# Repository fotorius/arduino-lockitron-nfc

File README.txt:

Author:   Alfredo Rius
License:  BSD(LICENSE)

    This is an implementation of the NFC breakout for the PN532 from Adafruit
    and the Lockitron platform to allow access to doors.

    This program is based on the readMifare.pde from Adafruit. It takes the
    first 4 bytes of a Mifare card uid and compares it to flash memory. Since
    it is saved to the flash, it will remember all cards even if the arduino
    is disconnected.

    This program is based on the arduino-lockitron-nfc shield located (Eagle
    files in https://github.com/devalfrz/arduino-lockitron-nfc).

    Buttons: (buttons are set to have a pullup resistor so they ar inverted)
      - LOCK_UNLOCK: This button will lock or unlock the system depending on its
          previous state.
          
      - SAVE_CARD: If it's pressed for 3 seconds while a card is read,
          it will either save the current card and blink 3 times or delete the
          card and blink one time for 2 seconds.
          
      - RESET_MEMORY: Keep this button pressed and this will clear all cards in
          memory.

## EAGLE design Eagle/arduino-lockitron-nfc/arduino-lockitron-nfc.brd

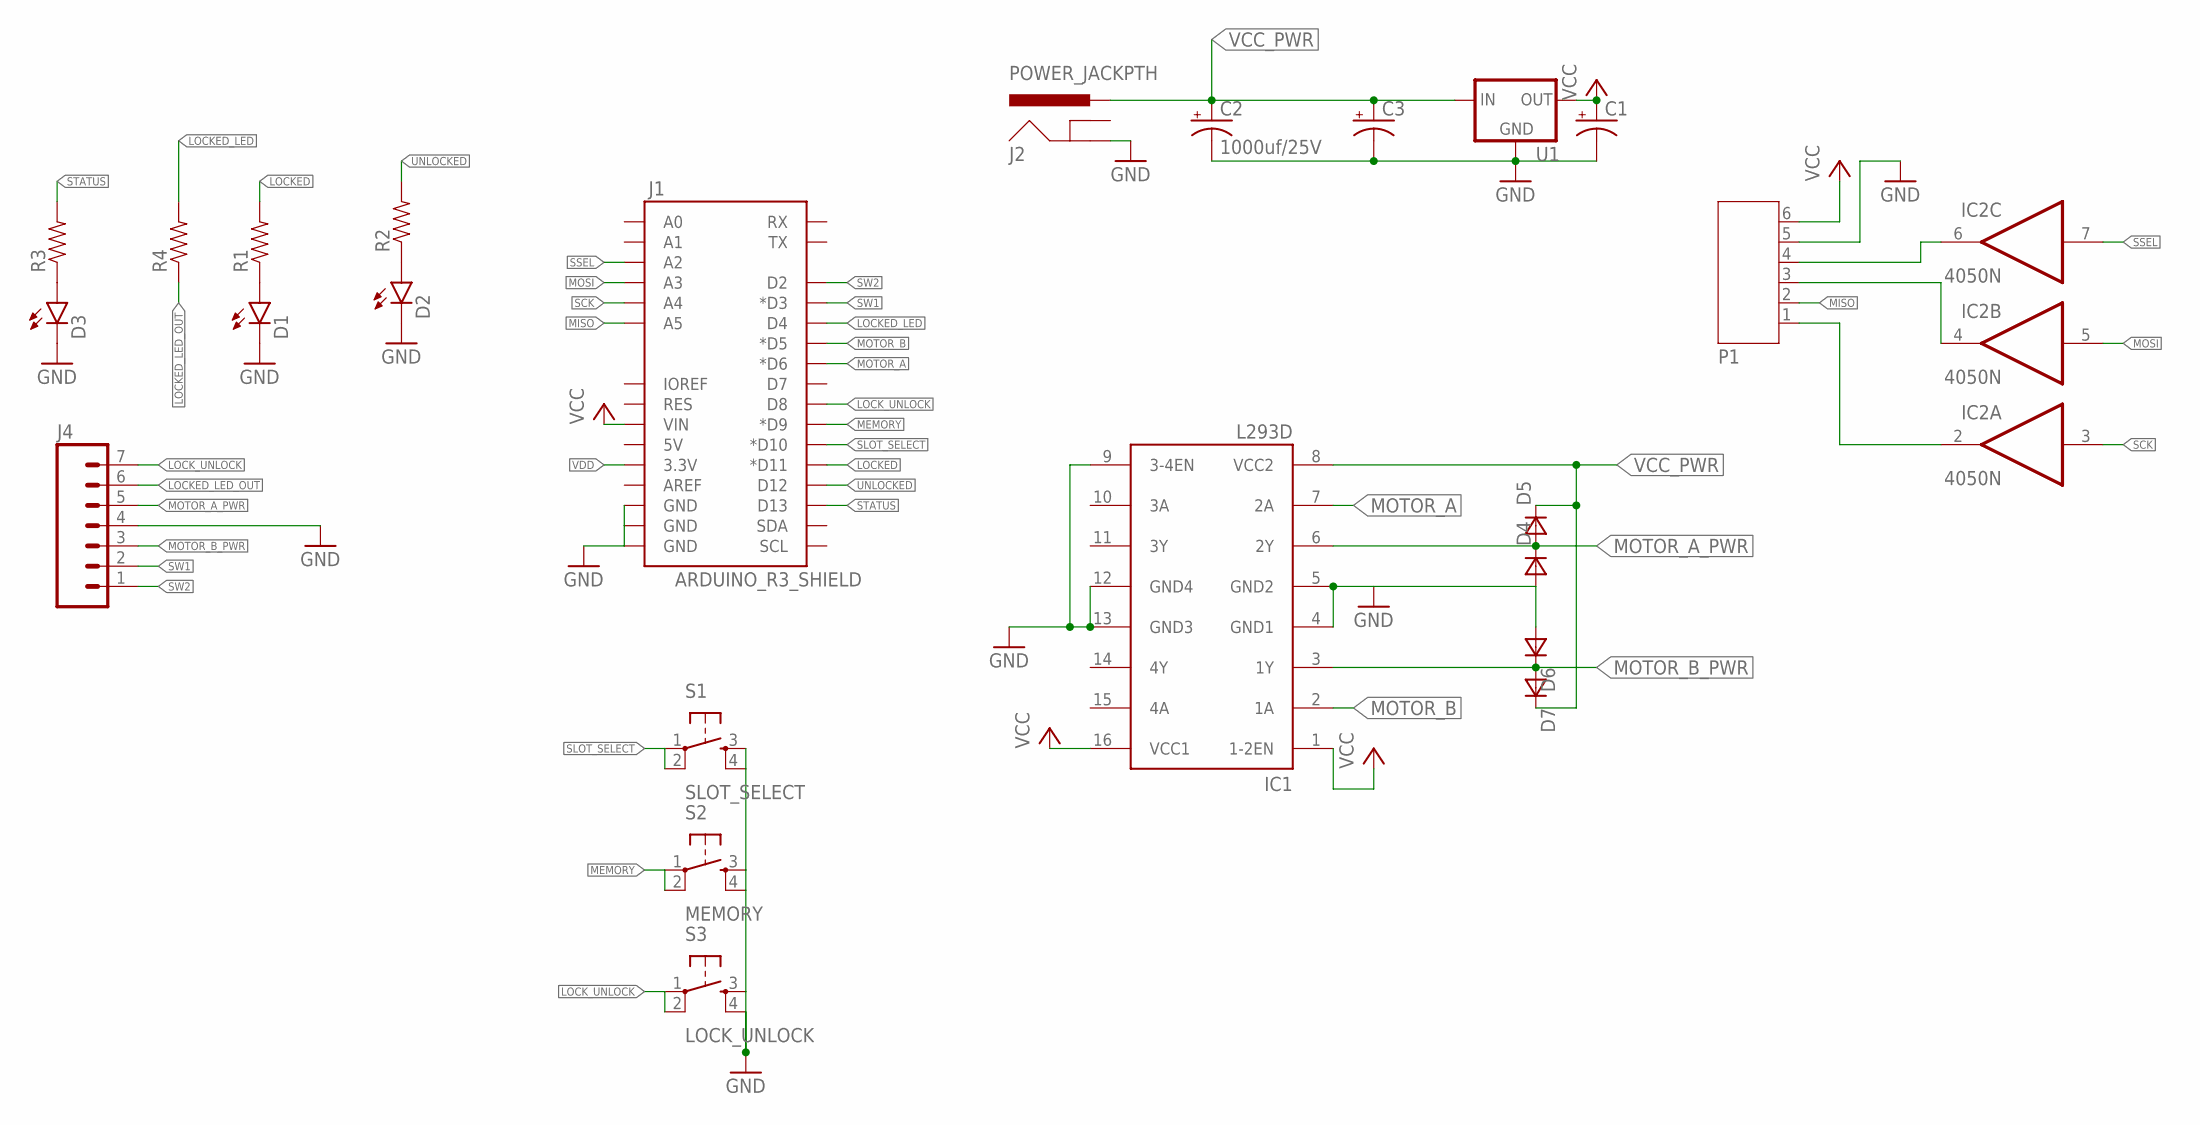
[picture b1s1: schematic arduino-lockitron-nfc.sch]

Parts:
C1, C3: 47UF-50V-20%(ELECT); PANASONIC_D
C2: 1000uf/25V; CPOL-RADIAL-1000UF-25V-KIT
D1, D2, D3: LED0603; LED-0603
D4, D5, D6, D7: DSOD323; SOD323
IC1: L293D; DIL16
IC2: 4050N; DIL16
J1: ARDUINO_R3_SHIELD; UNO_R3_SHIELD
J2: POWER_JACKPTH; POWER_JACK_PTH
J4: M07LONGPADS; 1X07_LONGPADS
P1: JST-PH6
R1, R2, R3, R4: RESISTOR0603; 0603-RES
S1: SLOT_SELECT; TACTILE-SWITCH-SMD
S2: MEMORY; TACTILE-SWITCH-SMD
S3: LOCK_UNLOCK; TACTILE-SWITCH-SMD
U1: V_REG_78XXSIDE; 78XXL

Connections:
LOCKED: J1.D11 (*D11), R1.2
LOCKED_LED: J1.D4, R4.2
LOCKED_LED_OUT: J4.6, R4.1
LOCK_UNLOCK: J1.D8, J4.7, S3.1, S3.2
MEMORY: J1.D9 (*D9), S2.1, S2.2
MISO: J1.A5, P1.2
MOSI: IC2.5 (I), J1.A3
MOTOR_A: IC1.7 (2A), J1.D6 (*D6)
MOTOR_A_PWR: D4.1 (C), D5.2 (A), IC1.6 (2Y), J4.5
MOTOR_B: IC1.2 (1A), J1.D5 (*D5)
MOTOR_B_PWR: D6.1 (C), D7.2 (A), IC1.3 (1Y), J4.3
unnamed: IC2.2 (O), P1.1
unnamed: IC2.4 (O), P1.3
unnamed: IC2.6 (O), P1.4
unnamed: D1.A, R1.1
unnamed: D3.A, R3.1
unnamed: D2.A, R2.1
SCK: IC2.3 (I), J1.A4
SLOT_SELECT: J1.D10 (*D10), S1.1, S1.2
SSEL: IC2.7 (I), J1.A2
STATUS: J1.D13, R3.2
SW1: J1.D3 (*D3), J4.2
SW2: J1.D2, J4.1
UNLOCKED: J1.D12, R2.2
VCC: C1.+, IC1.1 (1-2EN), IC1.16 (VCC1), J1.VIN, P1.6, U1.OUT
VCC_PWR: C2.+, C3.+, D5.1 (C), D7.1 (C), IC1.8 (VCC2), J2.PWR, U1.IN
VDD: IC2.1 (VDD), J1.3.3V
VSS: C1.-, C2.-, C3.-, D1.C, D2.C, D3.C, D4.2 (A), D6.2 (A), IC1.4 (GND1), IC1.5 (GND2), IC1.9 (3-4EN), IC1.12 (GND4), IC1.13 (GND3), IC2.8 (VSS), J1.GND@0 (GND), J1.GND@1 (GND), J1.GND@2 (GND), J2.GND, J4.4, P1.5, S1.3, S1.4, S2.3, S2.4, S3.3, S3.4, U1.GND

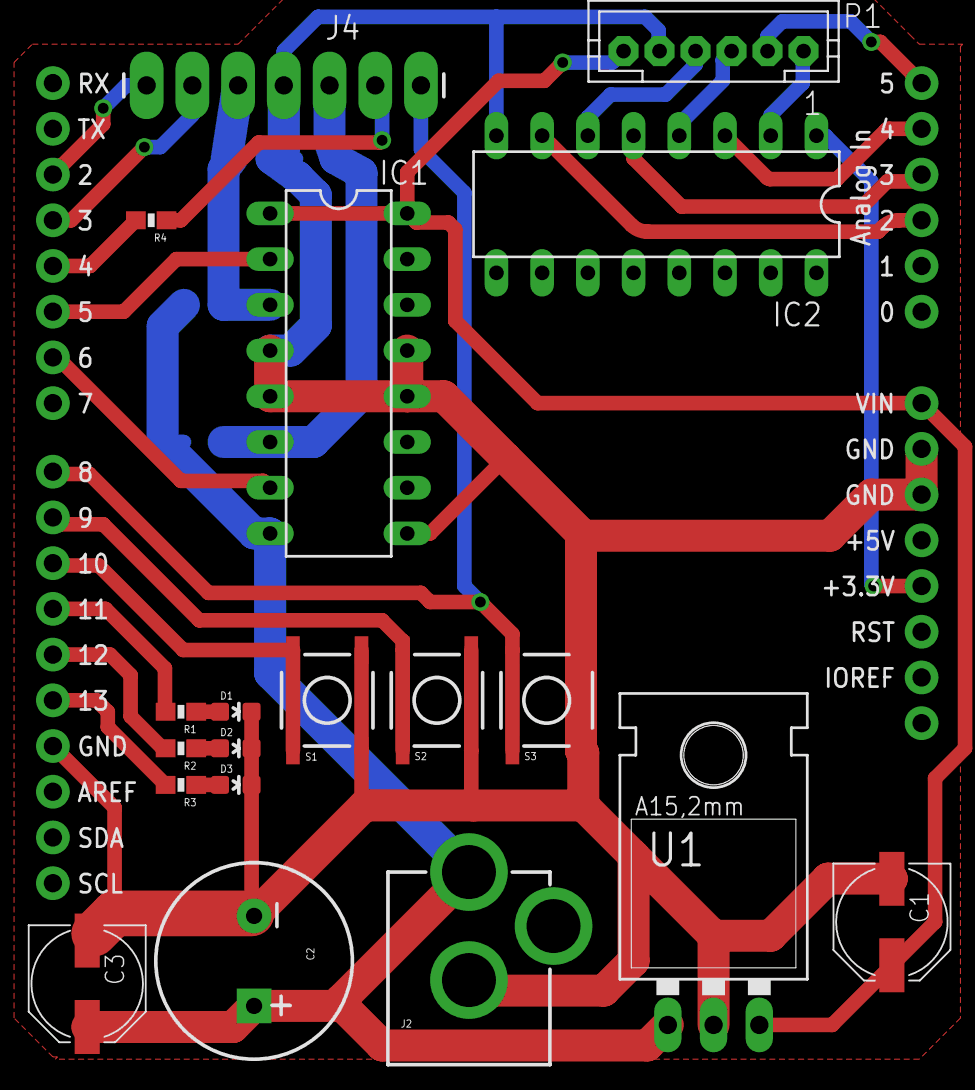
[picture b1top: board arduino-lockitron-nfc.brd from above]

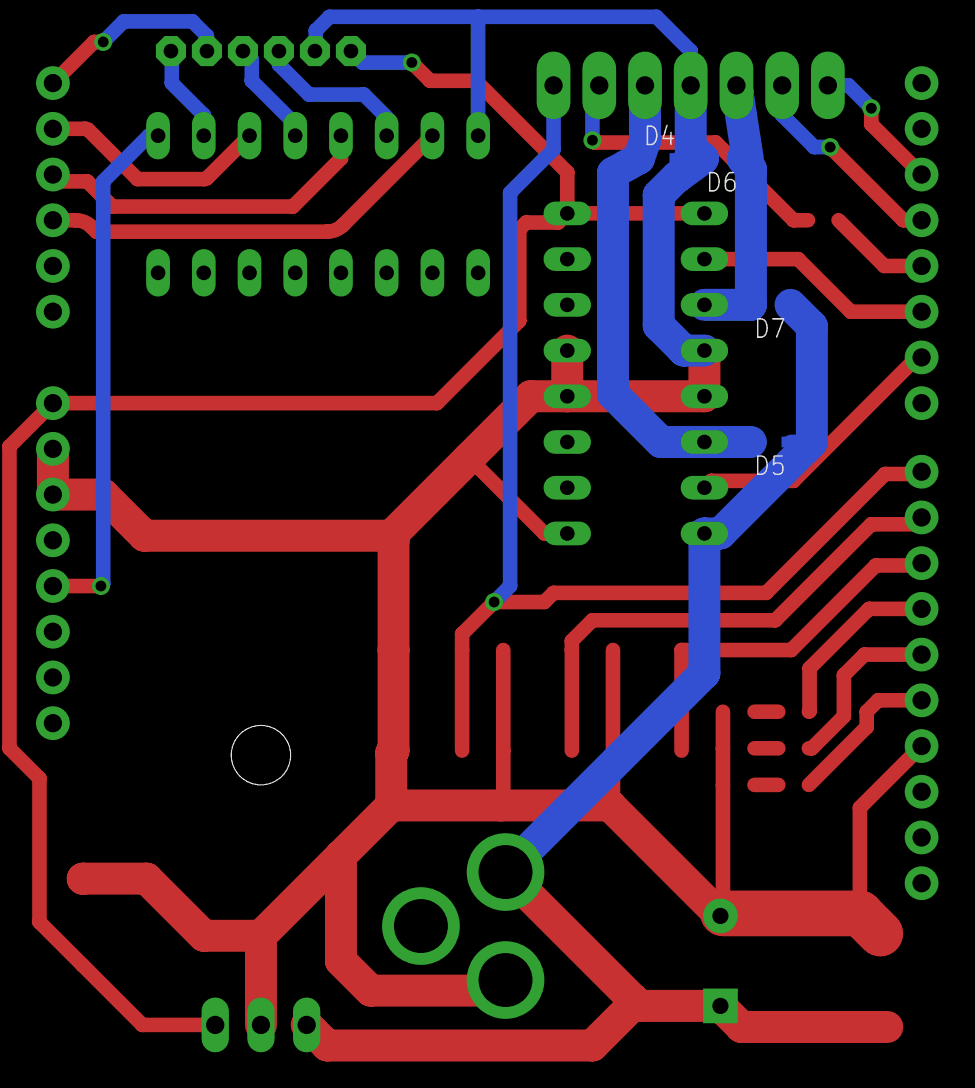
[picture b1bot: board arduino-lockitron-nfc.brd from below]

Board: 2 copper layers, 24 parts (4 on the bottom side), 28 nets.

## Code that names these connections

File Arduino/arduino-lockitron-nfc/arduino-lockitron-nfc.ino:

/**************************************************************************/
/*! 
    @file     arduino-lockitron-nfc
    @author   Alfredo Rius
    @license  BSD

    This is an implementation of the NFC breakout for the PN532 from Adafruit
    and the Lockitron platform to allow access to doors.

    This program is based on the arduino-lockitron-nfc shield located (Eagle
    files in https://github.com/devalfrz/arduino-lockitron-nfc).

    Buttons: (buttons are set to have a pullup resistor so they ar inverted)
      - LOCK_UNLOCK: This button will lock or unlock the system depending on its
          previous state.
          
      - SAVE_CARD: If it's pressed for 3 seconds while a card is read,
          it will either save the current card and blink 3 times or delete the
          card and blink one time for 2 seconds.
          
      - RESET_MEMORY: Keep this button pressed and this will clear all cards in
          memory.
          

*/
/**************************************************************************/

/**** INPUTS/OUTPUTS ****/
// Adafruit PN532 breakout board:
#define PN532_SCK  A4
#define PN532_MOSI A3
#define PN532_SS   A2
#define PN532_MISO A5
// Buttons
#define SLOT_SELECT 10
#define SAVE_CARD 9
#define STATUS_LED 13
#define UNLOCKED 12
#define LOCKED 11
// Lockitron
#define MOTOR_A 6
#define MOTOR_B 5
#define SW1 2
#define SW2 3
#define LOCK_UNLOCK 8

/**** Other definitions ****/
#define TOTAL_SLOTS 64 // Arbitrary number of slots available
#define SLOT_SIZE 4
//#define DEBUG // Will show output on terminal



#include <Wire.h>
#include <SPI.h>
#include <Adafruit_PN532.h>
#include <EEPROM.h>


// Adafruit PN532 init SPI
Adafruit_PN532 nfc(PN532_SCK, PN532_MISO, PN532_MOSI, PN532_SS);


int memory_slot = 0;
boolean state = 0;


void setup(void) {
  pinMode(SAVE_CARD,INPUT_PULLUP);
  pinMode(SLOT_SELECT,INPUT_PULLUP);
  pinMode(STATUS_LED,OUTPUT);
  pinMode(LOCKED,OUTPUT);
  pinMode(UNLOCKED,OUTPUT);
  pinMode(SW1,INPUT_PULLUP);
  pinMode(SW2,INPUT_PULLUP);
  pinMode(LOCK_UNLOCK,INPUT_PULLUP);
  pinMode(MOTOR_A,OUTPUT);
  pinMode(MOTOR_B,OUTPUT);
  
  #ifdef DEBUG
  Serial.begin(115200);
  #endif

  nfc.begin();

  uint32_t versiondata = nfc.getFirmwareVersion();
  if (! versiondata) {
    #ifdef DEBUG
    Serial.print("Didn't find PN53x board");
    #endif
    digitalWrite(STATUS_LED,HIGH);
    while (1); // halt
  }
  #ifdef DEBUG
  // Got ok data, print it out!
  Serial.print("Found chip PN5"); Serial.println((versiondata>>24) & 0xFF, HEX); 
  Serial.print("Firmware ver. "); Serial.print((versiondata>>16) & 0xFF, DEC); 
  Serial.print('.'); Serial.println((versiondata>>8) & 0xFF, DEC);
  #endif
  
  // configure board to read RFID tags
  nfc.SAMConfig();
}


void loop(void) {
  uint8_t success;
  uint8_t uid[] = { 0, 0, 0, 0, 0, 0, 0 };  // Buffer to store the returned UID
  uint8_t uidLength;    // Length of the UID (4 or 7 bytes depending on ISO14443A card type)
  int i,j;
  boolean save_delete = 0;
  boolean access_granted = 0;
  
  // Wait for an ISO14443A type cards (Mifare, etc.).  When one is found
  // 'uid' will be populated with the UID, and uidLength will indicate
  // if the uid is 4 bytes (Mifare Classic) or 7 bytes (Mifare Ultralight)
  success = nfc.readPassiveTargetID(PN532_MIFARE_ISO14443A, uid, &uidLength,100);
  
  save_delete = (success && !digitalRead(SAVE_CARD)) ? 1 : 0;
  
  if (success) {
    digitalWrite(STATUS_LED,HIGH);
    delay(100);
    digitalWrite(STATUS_LED,LOW);
    #ifdef DEBUG
    // Display some basic information about the card
    Serial.println("Found an ISO14443A card");
    Serial.print("  UID Length: ");Serial.print(uidLength, DEC);Serial.println(" bytes");
    Serial.print("  UID Value: ");
    nfc.PrintHex(uid, uidLength);
    Serial.println("");
    #endif
    memory_slot = check_card(uid);
    access_granted = (memory_slot == -1) ? 0 : 1;
    
    if(save_delete){
      access_granted = 0; //Reset Access
      #ifdef DEBUG
      Serial.println("Continue pressing to save or delete card");
      #endif
      delay(3000);
      if(!digitalRead(SAVE_CARD)){
        if(memory_slot == -1){
          memory_slot = save_card(uid);
          #ifdef DEBUG
          Serial.print("Save Card Slot: ");
          Serial.println(memory_slot+1);
          blink_n_times(memory_slot+1,STATUS_LED,250);
          delay(1000);
          #endif
          blink_n_times(3,STATUS_LED,100);
        }else{
          delete_card(memory_slot);
          #ifdef DEBUG
          Serial.println("Card deleted!");
          #endif
          blink_n_times(1,STATUS_LED,2000);
        }
      }
    }
    if(access_granted){
      #ifdef DEBUG
      Serial.println("Access Granted");
      #endif

      // Lock/Unlock system.
      digitalWrite(STATUS_LED,HIGH);
      state = lock(!state);
      digitalWrite(STATUS_LED,LOW);
      delay(100);
      #ifdef DEBUG
        if(check_card(uid)) blink_n_times(i+1,STATUS_LED,250); 
      #endif
    }else{
      #ifdef DEBUG
      Serial.println("Access Denied");
      #endif
    }
    access_granted = 0; //Reset Access
  }
  if(!digitalRead(LOCK_UNLOCK)){// Unlock or lock door
    state = lock(!state);
  }
  if(!digitalRead(RESET_MEMORY)){// Swipe memory
    digitalWrite(STATUS_LED,HIGH);
    delay(5000);
    digitalWrite(STATUS_LED,LOW);
    if(!digitalRead(RESET_MEMORY)){
      clear_memory();
      blink_n_times(4,STATUS_LED,100);
      delay(1000);
    }
  }
}

int check_card(uint8_t *uid){
  /* 
   *  Checks if card is saved, returns the address of the card if it saved
   *  or -1 if it is not found.
   */
  int i,j;
  int memory_offset;

  for(i=0;i<TOTAL_SLOTS;i++){
    memory_offset = i*SLOT_SIZE;
    for(j=0;j<SLOT_SIZE;j++){
      if(EEPROM.read(memory_offset+j)!=uid[j]) break;
    }
    if(j==SLOT_SIZE){
      return i;
    }
  }
  return -1;
}
int save_card(uint8_t *uid){
  /* 
   *  Saves card to empty slot
   */
  uint8_t blank_card[] = {0,0,0,0};
  int card_addr = check_card(uid);// Search card
  int i, new_addr, memory_offset;
  if(card_addr == -1){
    new_addr = check_card(blank_card);// Search for a empty slot
    if(new_addr != -1){
      memory_offset = SLOT_SIZE*new_addr;
      for(i=0;i<SLOT_SIZE;i++){
        EEPROM.write(memory_offset+i,uid[i]);
      }
    }
    return new_addr;
  }
  return -1;// Already saved

}
int delete_card(int addr){
  /* 
   *  Deletes card from memory slot (addr)
   */
  int memory_offset = SLOT_SIZE*addr;
  int i;

  for(i=0;i<SLOT_SIZE;i++){
    EEPROM.write(memory_offset+i,0);
  }
}
void clear_memory(void){
  int i;
  int total = TOTAL_SLOTS*SLOT_SIZE;
  for(i=0;i<total;i++){
    EEPROM.write(i,0);
  }
}
void blink_n_times(int n,int led_pin,int blink_interval){
  /*
   * Blink led_pin n times for blink_interval
   */
  int i;
  for(i=0;i<n;i++){
    digitalWrite(led_pin,HIGH);
    delay(blink_interval);
    digitalWrite(led_pin,LOW);
    delay(blink_interval);
  }
}

int lock(int state){
  /* 
   *  Opens or closes Lockitron door
   */
  digitalWrite(STATUS_LED, HIGH);
  digitalWrite(UNLOCKED, LOW);
  digitalWrite(LOCKED, LOW);
  digitalWrite(MOTOR_A, state);
  digitalWrite(MOTOR_B, !state);
  if(state){
    while(digitalRead(SW1));
    while(!digitalRead(SW2));
  }
  else{
    while(digitalRead(SW2));
    while(!digitalRead(SW1));
  }
  digitalWrite(MOTOR_A, LOW);
  digitalWrite(MOTOR_B, LOW);
  digitalWrite(STATUS_LED, LOW);
  digitalWrite(UNLOCKED, state);
  digitalWrite(LOCKED, !state);
  return state;
}

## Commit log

2016-02-01 Update README.txt
    Simplified card registration
2016-02-01 Simplified card registration

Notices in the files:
parts and their libraries:
SparkFun-Capacitors: Licensing: Creative Commons ShareAlike 4.0 International - https://creativecommons.org/licenses/by-sa/4.0
